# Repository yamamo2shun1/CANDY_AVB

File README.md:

# CANDY_AVB
## Description
This board is adopted Intel MAX10 series FPGA and Analog Devices SigmaDSP audio codec and then aimed at easier to prototyping and studying with a FPGA based on an audio signal and an ethernet.

A FPGA board in the market is too simple(it has only GPIO ports and
we have to make extended board by ourselves) or too high functionality
(DDR memory, HDMI, Gigabit ethernet...).

**I wanted simple FPGA board for sound and music.** So I started to develop this board.

## Specifications
* FPGA: Intel 10M16SAU(MAX10) x1
* SDRAM: Alliance Memory 64Mb(AS4C4M16SA-7BCN)
* ETH: TI DP83848 x1
* CODEC: Analog Devices ADAU1761 x2
* USB Serial: Silabs CP2102N x1
* CLOCK: 48MHz Crystal

## PCB

## Board

## Block Diagram

## License
<br /><span xmlns:dct="http://purl.org/dc/terms/" property="dct:title">CANDY_AVB</span> by <span xmlns:cc="http://creativecommons.org/ns#" property="cc:attributionName">Shunichi Yamamoto</span> is licensed under a <a rel="license" href="http://creativecommons.org/licenses/by/4.0/">Creative Commons Attribution 4.0 International License</a>.

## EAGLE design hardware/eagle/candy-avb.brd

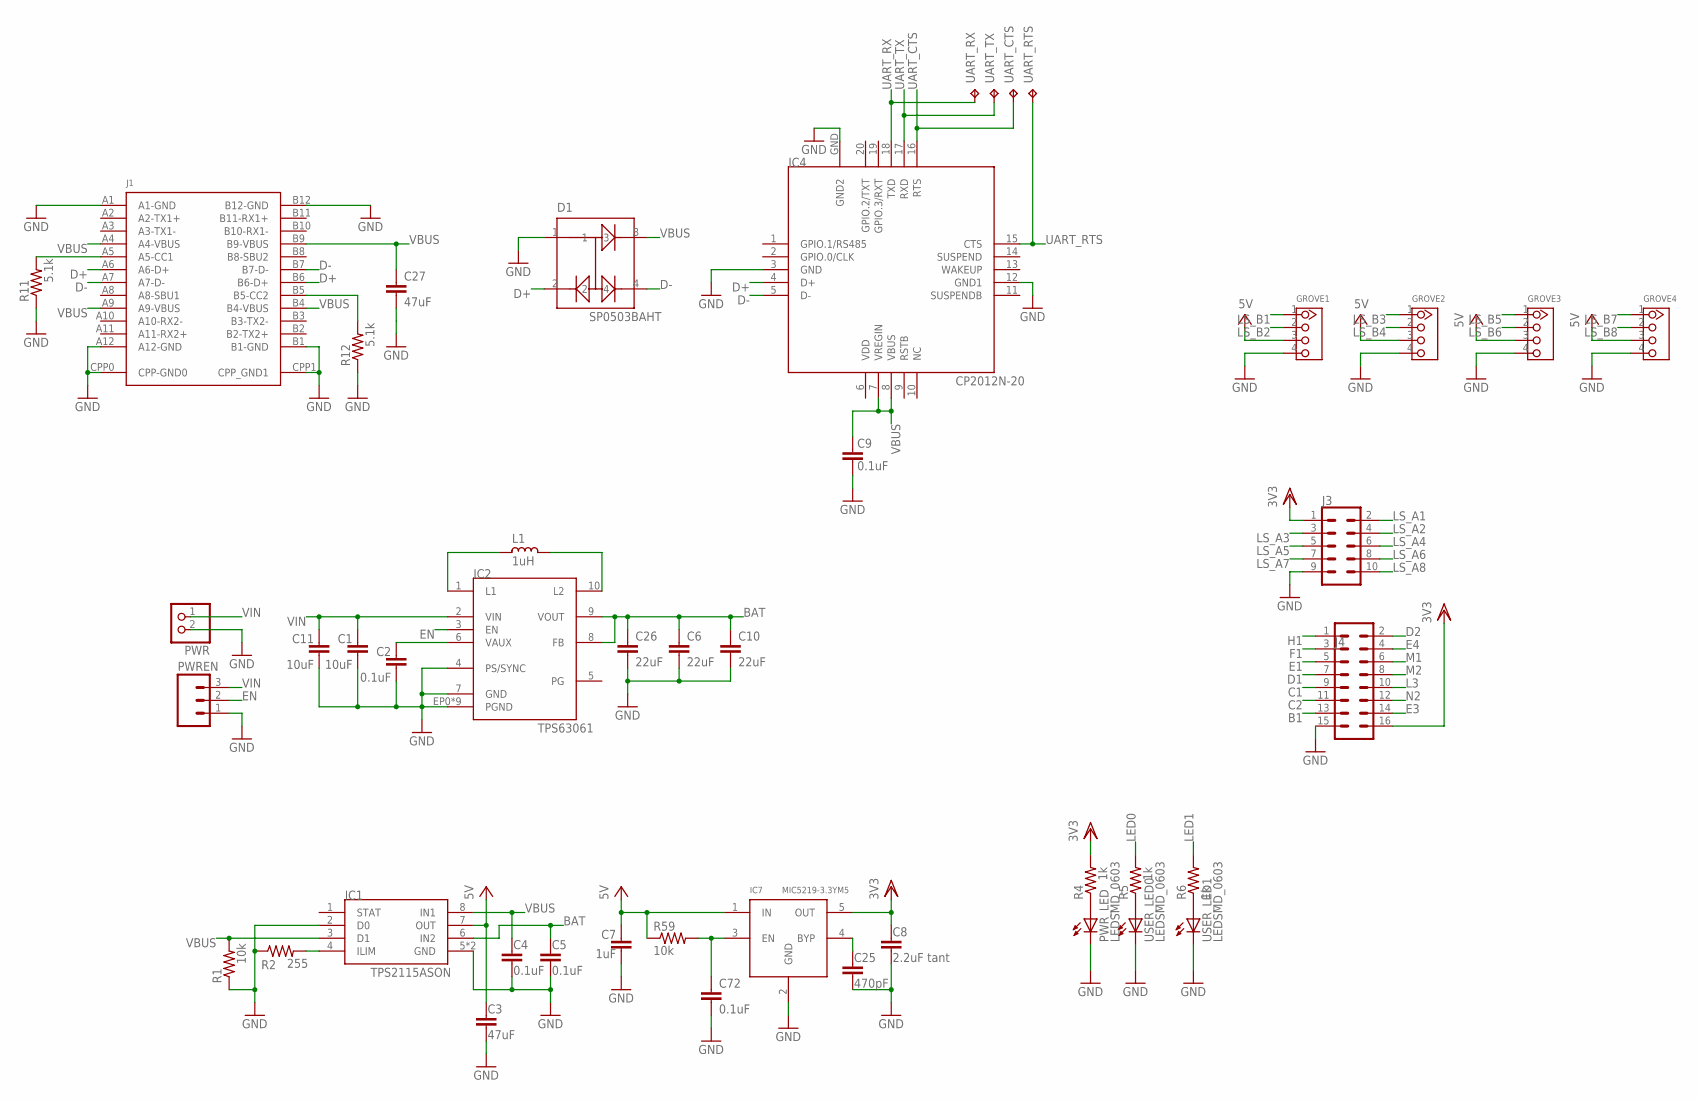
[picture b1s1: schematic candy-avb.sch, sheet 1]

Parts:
C1, C11: 10uF; C0805
C2, C4, C5, C9, C72: 0.1uF; C1608
C3, C27: 47uF; C1210
C6, C10, C26: 22uF; C0805
C7: 1uF; C1608
C8: 2.2uF tant; C1608
C25: 470pF; C1608
D1: SP0503BAHT; SOT143
GROVE1, GROVE2, GROVE3, GROVE4: 4P-2.0; SEEED_GROVE_4PIN_TH
IC1: TPS2115ASON; SON8
IC2: TPS63061; S-PDSO-N10
IC4: CP2012N-20; CP2102-QFN20
IC7: MIC5219-3.3YM5; SOT23-5
J1: USB_TYPEC_WE_632723
J3: CONN_05X2PTH; 2X5
J4: 2X6 FEMALE; 2X8
L1: 1uH; L4240
PWR: JST_2PIN-THM; JST-PH-2-THM
PWREN: M03PTH; 1X03
PWR_LED: LEDSMD_0603; CHIPLED_0603
R1, R59: 10k; 0402-RES
R2: 255; 0402-RES
R4, R5, R6: 1k; 0402-RES
R11, R12: 5.1k; 0402-RES
UART_CTS: TPB1,27; B1,27
UART_RTS: TPB1,27; B1,27
UART_RX: TPB1,27; B1,27
UART_TX: TPB1,27; B1,27
USER_LED0, USER_LED1: LEDSMD_0603; CHIPLED_0603

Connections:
B1: J4.13; also elsewhere on the board
BAT: C5.1, C6.1, C10.1, C26.1, IC1.6 (IN2), IC2.8 (FB), IC2.9 (VOUT)
C1: J4.9; also elsewhere on the board
C2: J4.11; also elsewhere on the board
D1: J4.7; also elsewhere on the board
D2: J4.2; also elsewhere on the board
D+: D1.2, IC4.4 (D+), J1.A6 (A6-D+), J1.B6 (B6-D+)
D-: D1.4, IC4.5 (D-), J1.A7 (A7-D-), J1.B7 (B7-D-)
E1: J4.5; also elsewhere on the board
E3: J4.14; also elsewhere on the board
E4: J4.4; also elsewhere on the board
EN: IC2.3 (EN), PWREN.2
EN1: C72.1, IC7.3 (EN), R59.2
F1: J4.3; also elsewhere on the board
GND: C1.2, C2.2, C3.2, C4.2, C5.2, C6.2, C7.2, C8.2, C9.2, C10.2, C11.2, C25.2, C26.2, C27.2, C72.2, D1.1, GROVE1.4, GROVE2.4, GROVE3.4, GROVE4.4, IC1.2 (D0), IC1.5 (GND), IC1.EP (GND), IC2.4 (PS/SYNC), IC2.7 (GND), IC2.EP0 (PGND), IC2.EP1 (PGND), IC2.EP2 (PGND), IC2.EP3 (PGND), IC2.EP4 (PGND), IC2.EP5 (PGND), IC2.EP6 (PGND), IC2.EP7 (PGND), IC2.EP8 (PGND), IC4.3 (GND), IC4.12 (GND1), IC4.GND (GND2), IC7.2 (GND), J1.A1 (A1-GND), J1.A12 (A12-GND), J1.B1 (B1-GND), J1.B12 (B12-GND), J1.CPP0 (CPP-GND0), J1.CPP1 (CPP_GND1), J3.9, J4.15, PWR.2 (1), PWREN.1, PWR_LED.C, R1.1, R2.1, R11.1, R12.1, USER_LED0.C, USER_LED1.C; also elsewhere on the board
H1: J4.1; also elsewhere on the board
L3: J4.10; also elsewhere on the board
LED0: R5.2; also elsewhere on the board
LED1: R6.2; also elsewhere on the board
LS_A1: J3.2; also elsewhere on the board
LS_A2: J3.4; also elsewhere on the board
LS_A3: J3.3; also elsewhere on the board
LS_A4: J3.6; also elsewhere on the board
LS_A5: J3.5; also elsewhere on the board
LS_A6: J3.8; also elsewhere on the board
LS_A7: J3.7; also elsewhere on the board
LS_A8: J3.10; also elsewhere on the board
LS_B1: GROVE1.1; also elsewhere on the board
LS_B2: GROVE1.2; also elsewhere on the board
LS_B3: GROVE2.1; also elsewhere on the board
LS_B4: GROVE2.2; also elsewhere on the board
LS_B5: GROVE3.1; also elsewhere on the board
LS_B6: GROVE3.2; also elsewhere on the board
LS_B7: GROVE4.1; also elsewhere on the board
LS_B8: GROVE4.2; also elsewhere on the board
M1: J4.6; also elsewhere on the board
M2: J4.8; also elsewhere on the board
N2: J4.12; also elsewhere on the board
unnamed: C2.1, IC2.6 (VAUX)
unnamed: C25.1, IC7.4 (BYP)
unnamed: PWR_LED.A, R4.1
unnamed: J1.A5 (A5-CC1), R11.2
unnamed: IC2.1 (L1), L1.2
unnamed: IC2.10 (L2), L1.1
unnamed: J1.B5 (B5-CC2), R12.2
unnamed: R6.1, USER_LED1.A
unnamed: R5.1, USER_LED0.A
unnamed: IC1.4 (ILIM), R2.2
UART_CTS: IC4.16 (RTS), UART_CTS.TP; also elsewhere on the board
UART_RTS: IC4.15 (CTS), UART_RTS.TP; also elsewhere on the board
UART_RX: IC4.18 (TXD), UART_RX.TP; also elsewhere on the board
UART_TX: IC4.17 (RXD), UART_TX.TP; also elsewhere on the board
VBUS: C4.1, C9.1, C27.1, D1.3, IC1.3 (D1), IC1.8 (IN1), IC4.7 (VREGIN), IC4.8 (VBUS), J1.A4 (A4-VBUS), J1.A9 (A9-VBUS), J1.B4 (B4-VBUS), J1.B9 (B9-VBUS), R1.2
VCC: C3.1, C7.1, GROVE1.3, GROVE2.3, GROVE3.3, GROVE4.3, IC1.7 (OUT), IC7.1 (IN), R59.1; also elsewhere on the board
VDD: C8.1, IC4.6 (VDD), IC7.5 (OUT), J3.1, J4.16, R4.2; also elsewhere on the board
VIN: C1.1, C11.1, IC2.2 (VIN), PWR.1 (2), PWREN.3

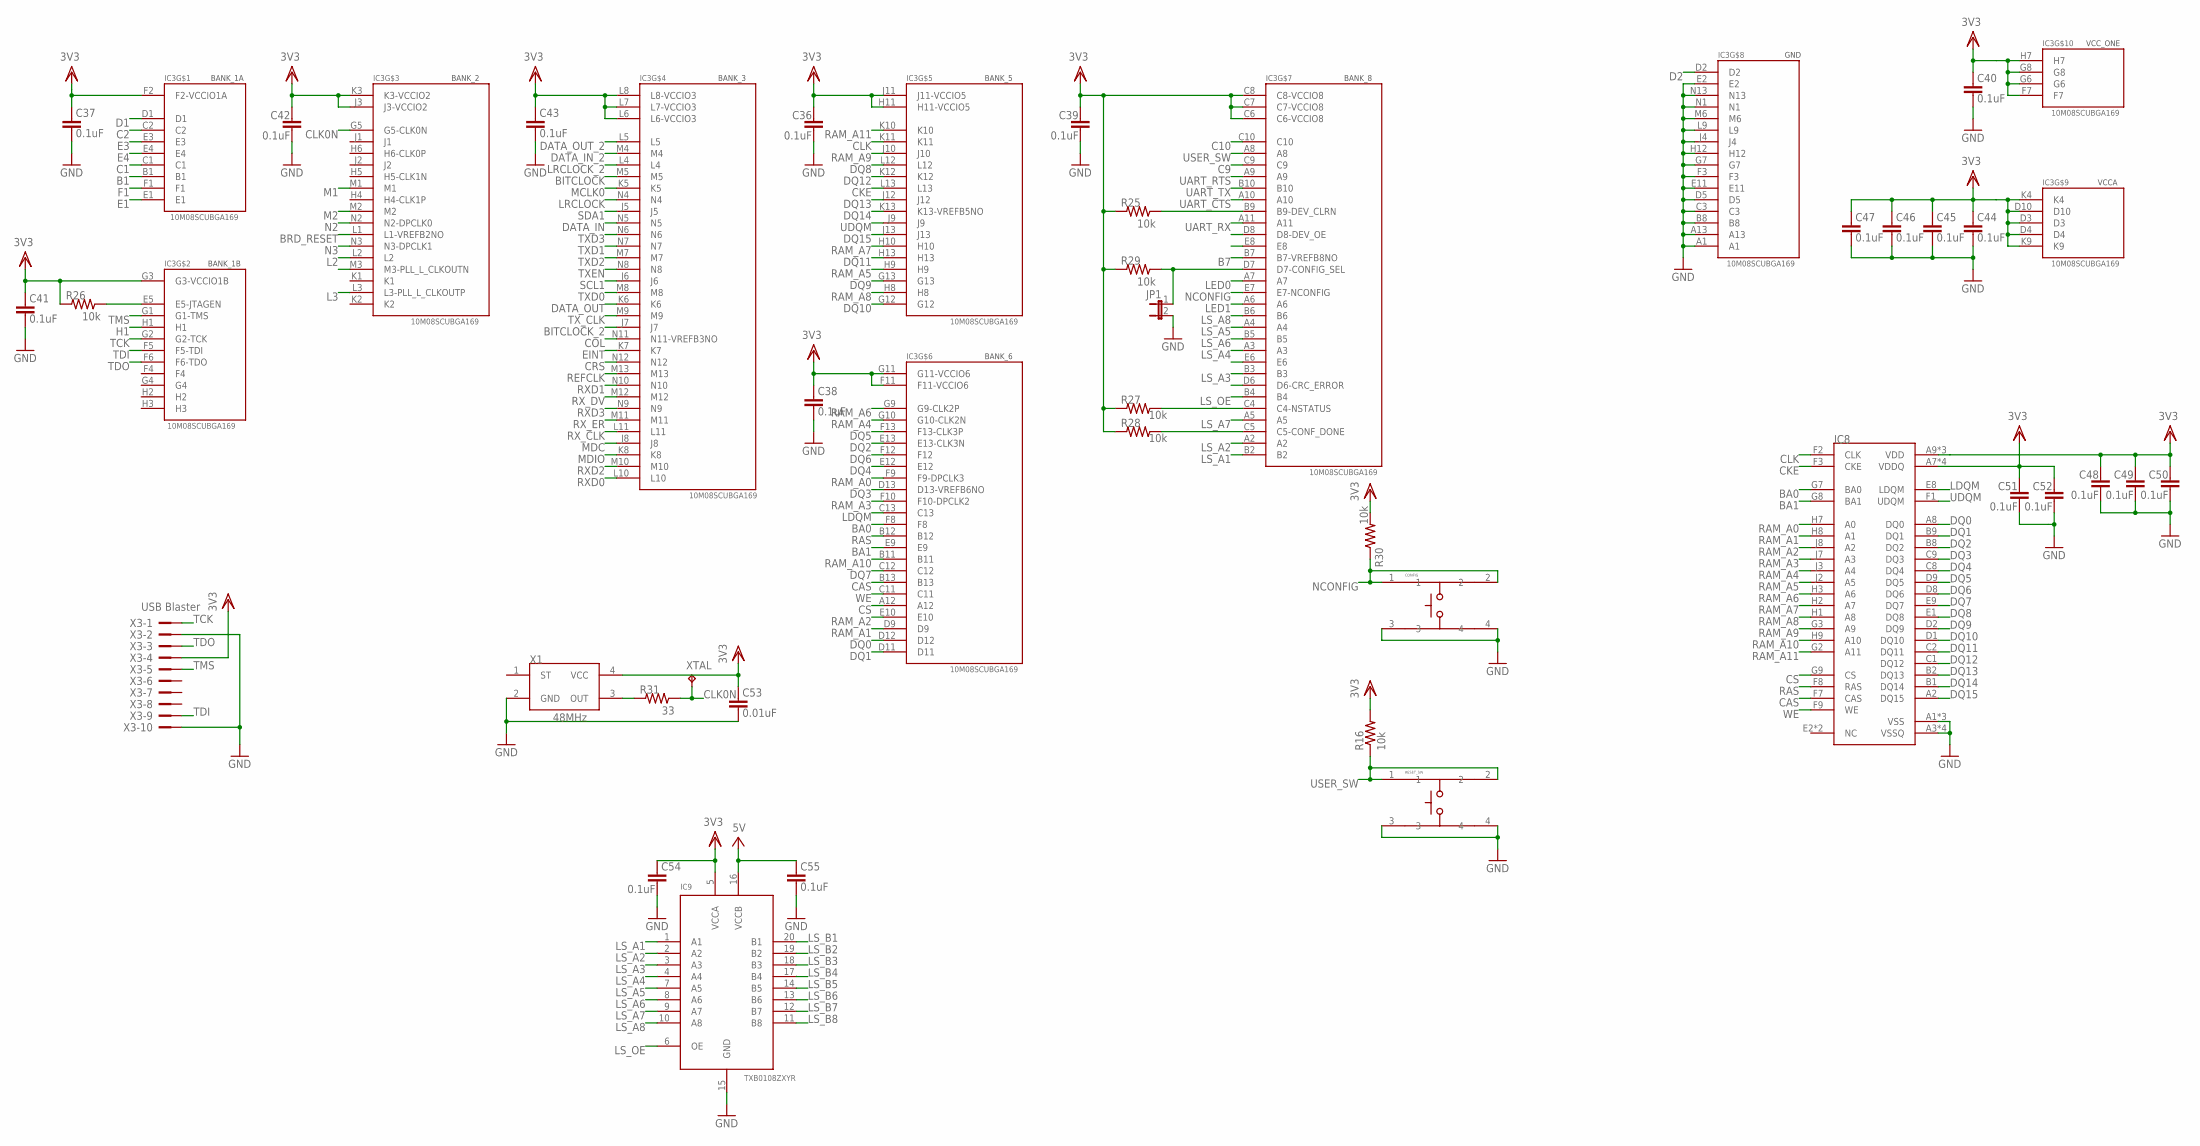
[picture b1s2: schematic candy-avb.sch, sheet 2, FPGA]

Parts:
C36, C37, C38, C39, C40, C41, C42, C43, C44, C45, C46, C47, C48, C49, C50, C51, C52, C54, C55: 0.1uF; C0402
C53: 0.01uF; C0402
CONFIG: TACTILE_SW_4PINSKRPABE010; SKRPABE010
IC3: 10M08SCUBGA169; MBGA169-MAX10
IC8: AS4C4M16SAFBGA54; FBGA54-AS4C4M16SA
IC9: TXB0108ZXYR; USON20
JP1: JUMPER-2SMD-NO; SJ_2S-NO
R16, R25, R26, R27, R28, R29, R30: 10k; 0402-RES
R31: 33; 0402-RES
RESET_SW: TACTILE_SW_4PINSKRPABE010; SKRPABE010
X1: 48MHz; SMD3225_4_EPSON
X3: USB Blaster; PAK100/2500-10
XTAL: TPPAD1-13; P1-13

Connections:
B1: IC3.B1; also elsewhere on the board
B7: IC3.B7 (B7-VREFB8NO)
BA0: IC3.F8, IC8.G7 (BA0)
BA1: IC3.E9, IC8.G8 (BA1)
BITCLOCK: IC3.M5; also elsewhere on the board
BITCLOCK_2: IC3.J7; also elsewhere on the board
BRD_RESET: IC3.L1 (L1-VREFB2NO); also elsewhere on the board
C1: IC3.C1; also elsewhere on the board
C2: IC3.C2; also elsewhere on the board
C9: IC3.C9
C10: IC3.C10
CAS: IC3.B13, IC8.F7 (CAS)
CKE: IC3.L13, IC8.F3 (CKE)
CLK: IC3.K11, IC8.F2 (CLK)
CLK0N: IC3.G5 (G5-CLK0N), R31.1, XTAL.TP
COL: IC3.N11 (N11-VREFB3NO); also elsewhere on the board
CRS: IC3.N12; also elsewhere on the board
CS: IC3.A12, IC8.G9 (CS)
D1: IC3.D1; also elsewhere on the board
D2: IC3.D2; also elsewhere on the board
DATA_IN: IC3.N5; also elsewhere on the board
DATA_IN_2: IC3.M4; also elsewhere on the board
DATA_OUT: IC3.K6; also elsewhere on the board
DATA_OUT_2: IC3.L5; also elsewhere on the board
DQ0: IC3.D12, IC8.A8 (DQ0)
DQ1: IC3.D11, IC8.B9 (DQ1)
DQ2: IC3.E13 (E13-CLK3N), IC8.B8 (DQ2)
DQ3: IC3.D13 (D13-VREFB6NO), IC8.C9 (DQ3)
DQ4: IC3.E12, IC8.C8 (DQ4)
DQ5: IC3.F13 (F13-CLK3P), IC8.D9 (DQ5)
DQ6: IC3.F12, IC8.D8 (DQ6)
DQ7: IC3.C12, IC8.E9 (DQ7)
DQ8: IC3.L12, IC8.E1 (DQ8)
DQ9: IC3.G13, IC8.D2 (DQ9)
DQ10: IC3.G12, IC8.D1 (DQ10)
DQ11: IC3.H13, IC8.C2 (DQ11)
DQ12: IC3.K12, IC8.C1 (DQ12)
DQ13: IC3.J12, IC8.B2 (DQ13)
DQ14: IC3.K13 (K13-VREFB5NO), IC8.B1 (DQ14)
DQ15: IC3.J13, IC8.A2 (DQ15)
E1: IC3.E1; also elsewhere on the board
E3: IC3.E3; also elsewhere on the board
E4: IC3.E4; also elsewhere on the board
EINT: IC3.K7; also elsewhere on the board
F1: IC3.F1; also elsewhere on the board
GND: C36.2, C37.2, C38.2, C39.2, C40.2, C41.2, C42.2, C43.2, C44.2, C45.2, C46.2, C47.2, C48.2, C49.2, C50.2, C51.2, C52.2, C53.2, C54.2, C55.2, CONFIG.3, CONFIG.4, IC3.A1, IC3.A13, IC3.B8, IC3.C3, IC3.D5, IC3.E2, IC3.E11, IC3.F3, IC3.G7, IC3.H12, IC3.J4, IC3.L9, IC3.M6, IC3.N1, IC3.N13, IC8.A1 (VSS), IC8.A3 (VSSQ), IC8.B7 (VSSQ), IC8.C3 (VSSQ), IC8.D7 (VSSQ), IC8.E3 (VSS), IC8.J1 (VSS), IC9.15 (GND), JP1.2, RESET_SW.3, RESET_SW.4, X1.2 (GND), X3.2, X3.10; also elsewhere on the board
H1: IC3.H1; also elsewhere on the board
L2: IC3.L2
L3: IC3.L3 (L3-PLL_L_CLKOUTP); also elsewhere on the board
LDQM: IC3.C13, IC8.E8 (LDQM)
LED0: IC3.A7; also elsewhere on the board
LED1: IC3.A6; also elsewhere on the board
LRCLOCK: IC3.N4; also elsewhere on the board
LRCLOCK_2: IC3.L4; also elsewhere on the board
LS_A1: IC3.B2, IC9.1 (A1); also elsewhere on the board
LS_A2: IC3.A2, IC9.2 (A2); also elsewhere on the board
LS_A3: IC3.B3, IC9.3 (A3); also elsewhere on the board
LS_A4: IC3.A3, IC9.4 (A4); also elsewhere on the board
LS_A5: IC3.A4, IC9.7 (A5); also elsewhere on the board
LS_A6: IC3.B5, IC9.8 (A6); also elsewhere on the board
LS_A7: IC3.A5, IC9.9 (A7); also elsewhere on the board
LS_A8: IC3.B6, IC9.10 (A8); also elsewhere on the board
LS_B1: IC9.20 (B1); also elsewhere on the board
LS_B2: IC9.19 (B2); also elsewhere on the board
LS_B3: IC9.18 (B3); also elsewhere on the board
LS_B4: IC9.17 (B4); also elsewhere on the board
LS_B5: IC9.14 (B5); also elsewhere on the board
LS_B6: IC9.13 (B6); also elsewhere on the board
LS_B7: IC9.12 (B7); also elsewhere on the board
LS_B8: IC9.11 (B8); also elsewhere on the board
LS_OE: IC3.B4, IC9.6 (OE)
M1: IC3.M1; also elsewhere on the board
M2: IC3.M2; also elsewhere on the board
MCLK0: IC3.K5; also elsewhere on the board
MDC: IC3.J8; also elsewhere on the board
MDIO: IC3.K8; also elsewhere on the board
N2: IC3.N2 (N2-DPCLK0); also elsewhere on the board
N3: IC3.N3 (N3-DPCLK1)
unnamed: IC3.E5 (E5-JTAGEN), R26.1
unnamed: IC3.B9 (B9-DEV_CLRN), R25.1
unnamed: IC3.C4 (C4-NSTATUS), R27.1
unnamed: IC3.C5 (C5-CONF_DONE), R28.1
unnamed: IC3.D7 (D7-CONFIG_SEL), JP1.1, R29.1
unnamed: R31.2, X1.3 (OUT)
NCONFIG: CONFIG.1, CONFIG.2, IC3.E7 (E7-NCONFIG), R30.1
RAM_A0: IC3.F9 (F9-DPCLK3), IC8.H7 (A0)
RAM_A1: IC3.D9, IC8.H8 (A1)
RAM_A2: IC3.E10, IC8.J8 (A2)
RAM_A3: IC3.F10 (F10-DPCLK2), IC8.J7 (A3)
RAM_A4: IC3.G10 (G10-CLK2N), IC8.J3 (A4)
RAM_A5: IC3.H9, IC8.J2 (A5)
RAM_A6: IC3.G9 (G9-CLK2P), IC8.H3 (A6)
RAM_A7: IC3.H10, IC8.H2 (A7)
RAM_A8: IC3.H8, IC8.H1 (A8)
RAM_A9: IC3.J10, IC8.G3 (A9)
RAM_A10: IC3.B11, IC8.H9 (A10)
RAM_A11: IC3.K10, IC8.G2 (A11)
RAS: IC3.B12, IC8.F8 (RAS)
REFCLK: IC3.M13; also elsewhere on the board
RXD0: IC3.L10; also elsewhere on the board
RXD1: IC3.N10; also elsewhere on the board
RXD2: IC3.M10; also elsewhere on the board
RXD3: IC3.N9; also elsewhere on the board
RX_CLK: IC3.L11; also elsewhere on the board
RX_DV: IC3.M12; also elsewhere on the board
RX_ER: IC3.M11; also elsewhere on the board
SCL1: IC3.J6; also elsewhere on the board
SDA1: IC3.J5; also elsewhere on the board
TCK: IC3.G2 (G2-TCK), X3.1
TDI: IC3.F5 (F5-TDI), X3.9
TDO: IC3.F6 (F6-TDO), X3.3
TMS: IC3.G1 (G1-TMS), X3.5
TXD0: IC3.M8; also elsewhere on the board
TXD1: IC3.N7; also elsewhere on the board
TXD2: IC3.M7; also elsewhere on the board
TXD3: IC3.N6; also elsewhere on the board
TXEN: IC3.N8; also elsewhere on the board
TX_CLK: IC3.M9; also elsewhere on the board
UART_CTS: IC3.A10; also elsewhere on the board
UART_RTS: IC3.A9; also elsewhere on the board
UART_RX: IC3.A11; also elsewhere on the board
UART_TX: IC3.B10; also elsewhere on the board
UDQM: IC3.J9, IC8.F1 (UDQM)
USER_SW: IC3.A8, R16.1, RESET_SW.1, RESET_SW.2
VCC: C55.1, IC9.16 (VCCB); also elsewhere on the board
VDD: C36.1, C37.1, C38.1, C39.1, C40.1, C41.1, C42.1, C43.1, C44.1, C45.1, C46.1, C47.1, C48.1, C49.1, C50.1, C51.1, C52.1, C53.1, C54.1, IC3.C6 (C6-VCCIO8), IC3.C7 (C7-VCCIO8), IC3.C8 (C8-VCCIO8), IC3.D3, IC3.D4, IC3.D10, IC3.F2 (F2-VCCIO1A), IC3.F7, IC3.F11 (F11-VCCIO6), IC3.G3 (G3-VCCIO1B), IC3.G6, IC3.G8, IC3.G11 (G11-VCCIO6), IC3.H7, IC3.H11 (H11-VCCIO5), IC3.J3 (J3-VCCIO2), IC3.J11 (J11-VCCIO5), IC3.K3 (K3-VCCIO2), IC3.K4, IC3.K9, IC3.L6 (L6-VCCIO3), IC3.L7 (L7-VCCIO3), IC3.L8 (L8-VCCIO3), IC8.A7 (VDDQ), IC8.A9 (VDD), IC8.B3 (VDDQ), IC8.C7 (VDDQ), IC8.D3 (VDDQ), IC8.E7 (VDD), IC8.J9 (VDD), IC9.5 (VCCA), R16.2, R25.2, R26.2, R27.2, R28.2, R29.2, R30.2, X1.4 (VCC), X3.4; also elsewhere on the board
WE: IC3.C11, IC8.F9 (WE)

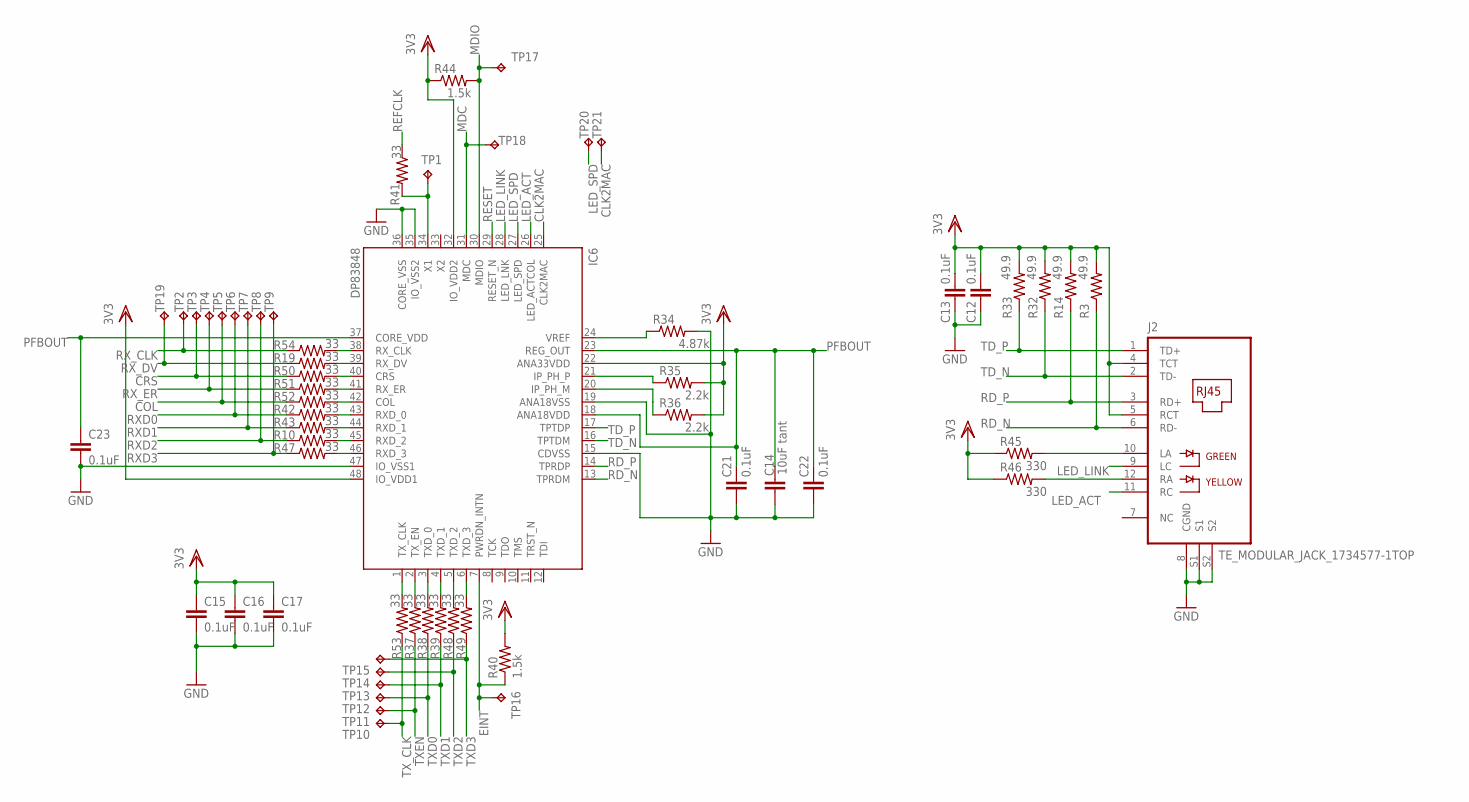
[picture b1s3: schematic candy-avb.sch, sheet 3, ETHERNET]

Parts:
C12, C13, C15, C16, C17, C21, C22, C23: 0.1uF; C0402
C14: 10uF tant; C0603
IC6: DP83848; LQFP48
J2: TE_MODULAR_JACK_1734577-1TOP; TE_MODULAR_JACK_1734577-1
R3, R14, R32, R33: 49.9; 0402-RES
R10, R19, R37, R38, R39, R41, R42, R43, R47, R48, R49, R50, R51, R52, R53, R54: 33; 0402-RES
R34: 4.87k; 0402-RES
R35, R36: 2.2k; 0402-RES
R40, R44: 1.5k; 0402-RES
R45, R46: 330; 0402-RES
TP1: TPPAD1-13; P1-13
TP2, TP3, TP4, TP5, TP6, TP7, TP8, TP9, TP10, TP11, TP12, TP13, TP14, TP15, TP16, TP17, TP18, TP19, TP20, TP21: TPB1,27; B1,27

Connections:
CLK2MAC: IC6.25 (CLK2MAC), TP21.TP
COL: R52.1, TP5.TP; also elsewhere on the board
CRS: R50.1, TP3.TP; also elsewhere on the board
EINT: IC6.7 (PWRDN_INTN), R40.1, TP16.TP; also elsewhere on the board
GND: C12.2, C13.2, C14.2, C15.2, C16.2, C17.2, C21.2, C22.2, C23.2, IC6.15 (CDVSS), IC6.19 (ANA18VSS), IC6.35 (IO_VSS2), IC6.36 (CORE_VSS), IC6.47 (IO_VSS1), J2.8 (CGND), J2.S1, J2.S2, R34.2; also elsewhere on the board
LED_ACT: IC6.26 (LED_ACTCOL), J2.11 (RC)
LED_LINK: IC6.28 (LED_LNK), J2.9 (LC)
LED_SPD: IC6.27 (LED_SPD), TP20.TP
MDC: IC6.31 (MDC), TP18.TP; also elsewhere on the board
MDIO: IC6.30 (MDIO), R44.2, TP17.TP; also elsewhere on the board
unnamed: IC6.20 (IP_PH_M), R36.1
unnamed: IC6.39 (RX_DV), R19.2
unnamed: IC6.4 (TXD_1), R39.2
unnamed: IC6.45 (RXD_2), R10.2
unnamed: IC6.46 (RXD_3), R47.2
unnamed: IC6.3 (TXD_0), R38.2
unnamed: IC6.2 (TX_EN), R37.2
unnamed: IC6.34 (X1), R41.2, TP1.TP
unnamed: IC6.43 (RXD_0), R42.2
unnamed: IC6.5 (TXD_2), R48.2
unnamed: J2.10 (LA), R45.2
unnamed: J2.12 (RA), R46.2
unnamed: IC6.44 (RXD_1), R43.2
unnamed: IC6.21 (IP_PH_P), R35.1
unnamed: IC6.24 (VREF), R34.1
unnamed: IC6.6 (TXD_3), R49.2
unnamed: IC6.42 (COL), R52.2
unnamed: IC6.41 (RX_ER), R51.2
unnamed: IC6.40 (CRS), R50.2
unnamed: IC6.38 (RX_CLK), R54.2
PFBOUT: C14.1, C21.1, C22.1, C23.1, IC6.18 (ANA18VDD), IC6.23 (REG_OUT), IC6.37 (CORE_VDD)
RD_N: IC6.13 (TPRDM), J2.6 (RD-), R3.1
RD_P: IC6.14 (TPRDP), J2.3 (RD+), R14.1
REFCLK: R41.1; also elsewhere on the board
RESET: IC6.29 (RESET_N)
RXD0: R42.1, TP6.TP; also elsewhere on the board
RXD1: R43.1, TP7.TP; also elsewhere on the board
RXD2: R10.1, TP8.TP; also elsewhere on the board
RXD3: R47.1, TP9.TP; also elsewhere on the board
RX_CLK: R54.1, TP2.TP; also elsewhere on the board
RX_DV: R19.1, TP19.TP; also elsewhere on the board
RX_ER: R51.1, TP4.TP; also elsewhere on the board
TD_N: IC6.16 (TPTDM), J2.2 (TD-), R32.1
TD_P: IC6.17 (TPTDP), J2.1 (TD+), R33.1
TXCLK: IC6.1 (TX_CLK), R53.2
TXD0: R38.1, TP12.TP; also elsewhere on the board
TXD1: R39.1, TP13.TP; also elsewhere on the board
TXD2: R48.1, TP14.TP; also elsewhere on the board
TXD3: R49.1, TP15.TP; also elsewhere on the board
TXEN: R37.1, TP11.TP; also elsewhere on the board
TX_CLK: R53.1, TP10.TP; also elsewhere on the board
VDD: C12.1, C13.1, C15.1, C16.1, C17.1, IC6.22 (ANA33VDD), IC6.32 (IO_VDD2), IC6.48 (IO_VDD1), J2.4 (TCT), J2.5 (RCT), R3.2, R14.2, R32.2, R33.2, R35.2, R36.2, R40.2, R44.1, R45.1, R46.1; also elsewhere on the board

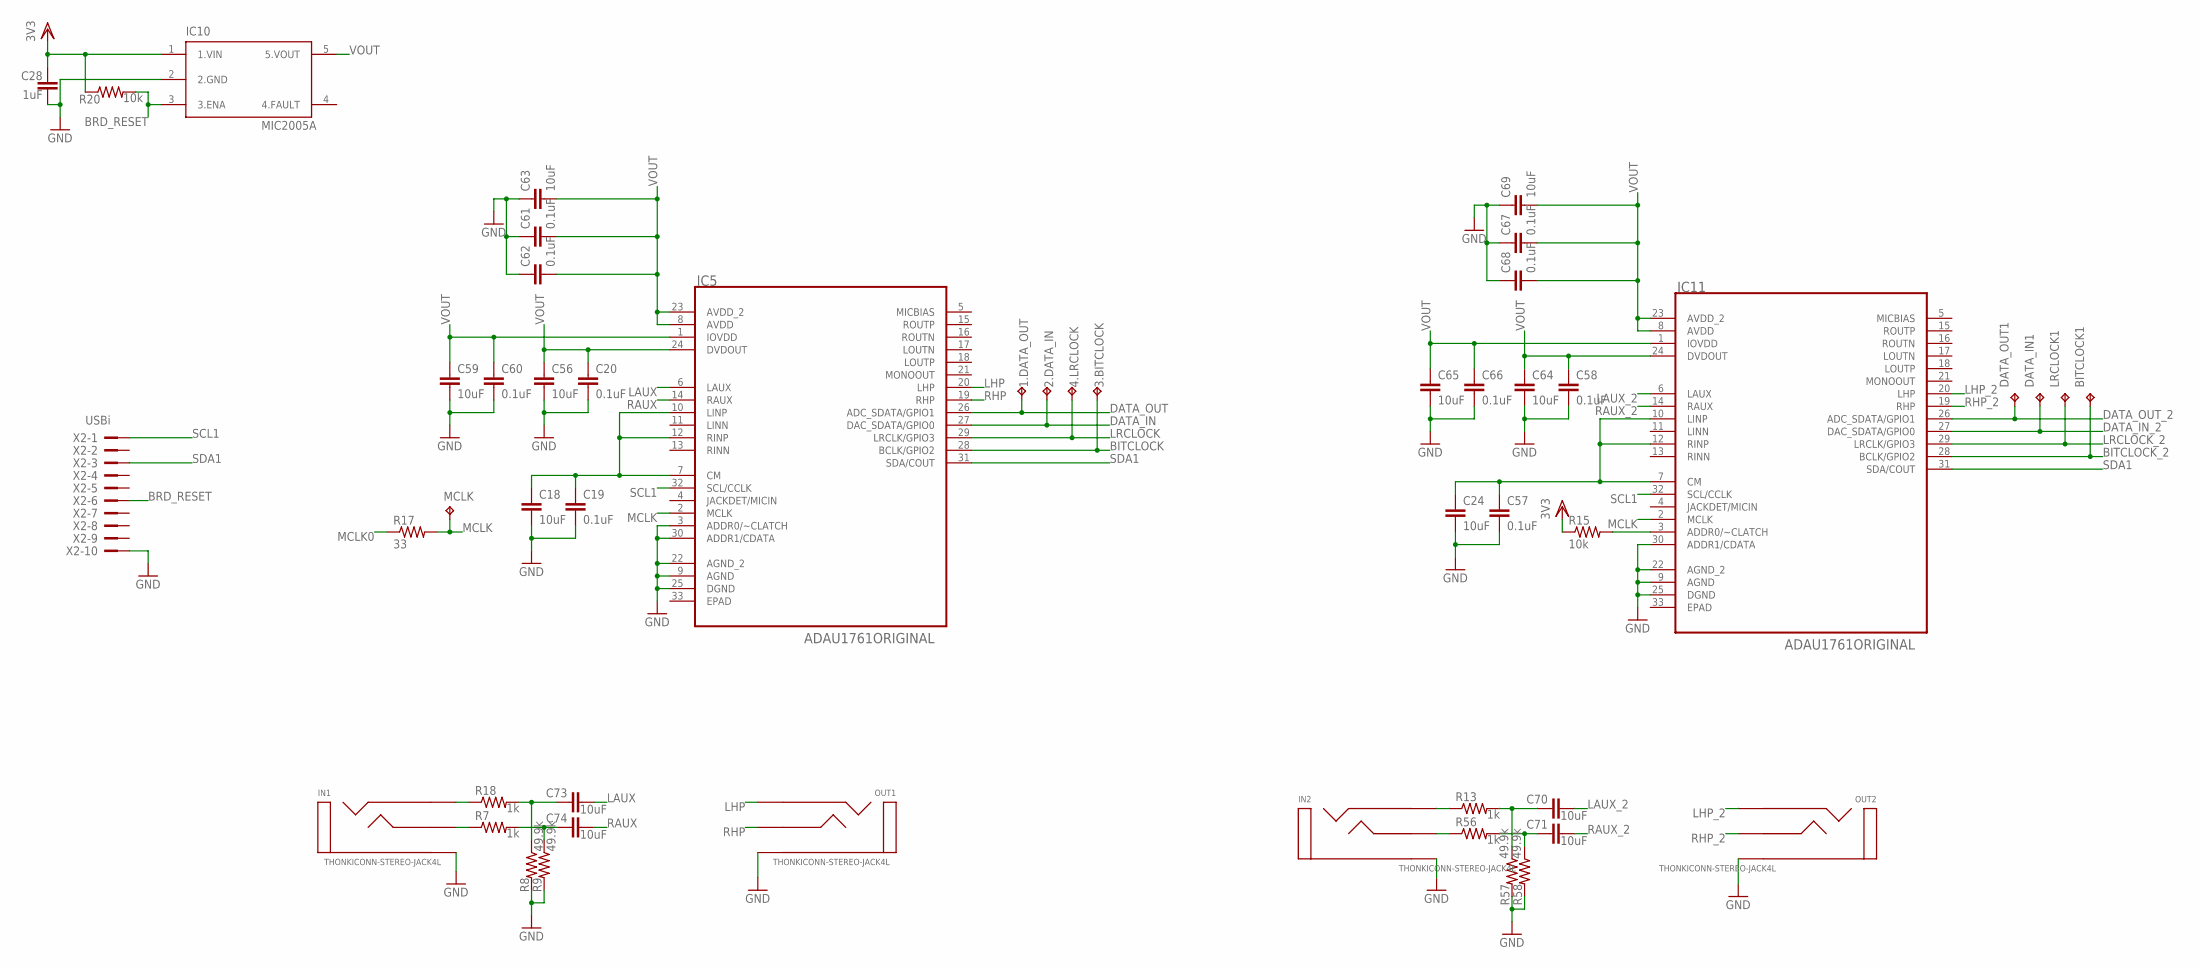
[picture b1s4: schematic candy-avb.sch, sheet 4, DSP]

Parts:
1.DATA_OUT, 2.DATA_IN, 3.BITCLOCK, 4.LRCLOCK: TPB1,27; B1,27
BITCLOCK1: TPB1,27; B1,27
C18, C24, C56, C59, C63, C64, C65, C69: 10uF; C0603
C19, C20, C57, C58, C60, C61, C62, C66, C67, C68: 0.1uF; C0402
C28: 1uF; C0603
C70, C71, C73, C74: 10uF; C1608
DATA_IN1: TPB1,27; B1,27
DATA_OUT1: TPB1,27; B1,27
IC5, IC11: ADAU1761ORIGINAL; QFN50_500X500_33_O
IC10: MIC2005A; SOT23-5
IN1, IN2: THONKICONN-STEREO-JACK4L; THONKICONN-JACK-4
LRCLOCK1: TPB1,27; B1,27
MCLK: TPPAD1-13; P1-13
OUT1, OUT2: THONKICONN-STEREO-JACK4L; THONKICONN-JACK-4
R7, R13, R18, R56: 1k; 0402-RES
R8, R9, R57, R58: 49.9k; 0402-RES
R15, R20: 10k; 0402-RES
R17: 33; 0402-RES
X2: USBi; PAK100/2500-10

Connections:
BITCLOCK: 3.BITCLOCK.TP, IC5.28 (BCLK/GPIO2); also elsewhere on the board
BITCLOCK_2: BITCLOCK1.TP, IC11.28 (BCLK/GPIO2); also elsewhere on the board
BRD_RESET: IC10.3 (3.ENA), R20.2, X2.6; also elsewhere on the board
DATA_IN: 2.DATA_IN.TP, IC5.27 (DAC_SDATA/GPIO0); also elsewhere on the board
DATA_IN_2: DATA_IN1.TP, IC11.27 (DAC_SDATA/GPIO0); also elsewhere on the board
DATA_OUT: 1.DATA_OUT.TP, IC5.26 (ADC_SDATA/GPIO1); also elsewhere on the board
DATA_OUT_2: DATA_OUT1.TP, IC11.26 (ADC_SDATA/GPIO1); also elsewhere on the board
GND: C18.2, C19.2, C20.2, C24.2, C28.2, C56.2, C57.2, C58.2, C59.2, C60.2, C61.1, C62.1, C63.1, C64.2, C65.2, C66.2, C67.1, C68.1, C69.1, IC5.3 (ADDR0/~CLATCH), IC5.9 (AGND), IC5.22 (AGND_2), IC5.25 (DGND), IC5.30 (ADDR1/CDATA), IC10.2 (2.GND), IC11.9 (AGND), IC11.22 (AGND_2), IC11.25 (DGND), IC11.30 (ADDR1/CDATA), IN1.1B (1.SLEEVE), IN1.1T (1.SLEEVE), IN2.1B (1.SLEEVE), IN2.1T (1.SLEEVE), OUT1.1B (1.SLEEVE), OUT1.1T (1.SLEEVE), OUT2.1B (1.SLEEVE), OUT2.1T (1.SLEEVE), R8.2, R9.2, R57.2, R58.2, X2.10; also elsewhere on the board
LAUX: C73.2, IC5.6 (LAUX)
LAUX_2: C70.2, IC11.6 (LAUX)
LHP: IC5.20 (LHP), OUT1.3B (3.RING), OUT1.3T (3.RING)
LHP_2: IC11.20 (LHP), OUT2.3B (3.RING), OUT2.3T (3.RING)
LRCLOCK: 4.LRCLOCK.TP, IC5.29 (LRCLK/GPIO3); also elsewhere on the board
LRCLOCK_2: IC11.29 (LRCLK/GPIO3), LRCLOCK1.TP; also elsewhere on the board
MCLK: IC5.2 (MCLK), IC11.2 (MCLK), MCLK.TP, R17.2
MCLK0: R17.1; also elsewhere on the board
unnamed: IC11.3 (ADDR0/~CLATCH), R15.2
unnamed: C18.1, C19.1, IC5.7 (CM), IC5.10 (LINP), IC5.12 (RINP)
unnamed: IN1.3B (3.RING), IN1.3T (3.RING), R18.1
unnamed: IN1.2B (2.TIP), IN1.2T (2.TIP), R7.1
unnamed: C24.1, C57.1, IC11.7 (CM), IC11.10 (LINP), IC11.12 (RINP)
unnamed: C70.1, R13.2, R57.1
unnamed: C71.1, R56.2, R58.1
unnamed: IN2.3B (3.RING), IN2.3T (3.RING), R13.1
unnamed: IN2.2B (2.TIP), IN2.2T (2.TIP), R56.1
unnamed: C73.1, R8.1, R18.2
unnamed: C74.1, R7.2, R9.1
RAUX: C74.2, IC5.14 (RAUX)
RAUX_2: C71.2, IC11.14 (RAUX)
RHP: IC5.19 (RHP), OUT1.2B (2.TIP), OUT1.2T (2.TIP)
RHP_2: IC11.19 (RHP), OUT2.2B (2.TIP), OUT2.2T (2.TIP)
SCL1: IC5.32 (SCL/CCLK), IC11.32 (SCL/CCLK), X2.1; also elsewhere on the board
SDA1: IC5.31 (SDA/COUT), IC11.31 (SDA/COUT), X2.3; also elsewhere on the board
VDD: C28.1, IC10.1 (1.VIN), R15.1, R20.1; also elsewhere on the board
VOUT: C20.1, C56.1, C58.1, C59.1, C60.1, C61.2, C62.2, C63.2, C64.1, C65.1, C66.1, C67.2, C68.2, C69.2, IC5.1 (IOVDD), IC5.8 (AVDD), IC5.23 (AVDD_2), IC5.24 (DVDOUT), IC10.5 (5.VOUT), IC11.1 (IOVDD), IC11.8 (AVDD), IC11.23 (AVDD_2), IC11.24 (DVDOUT)

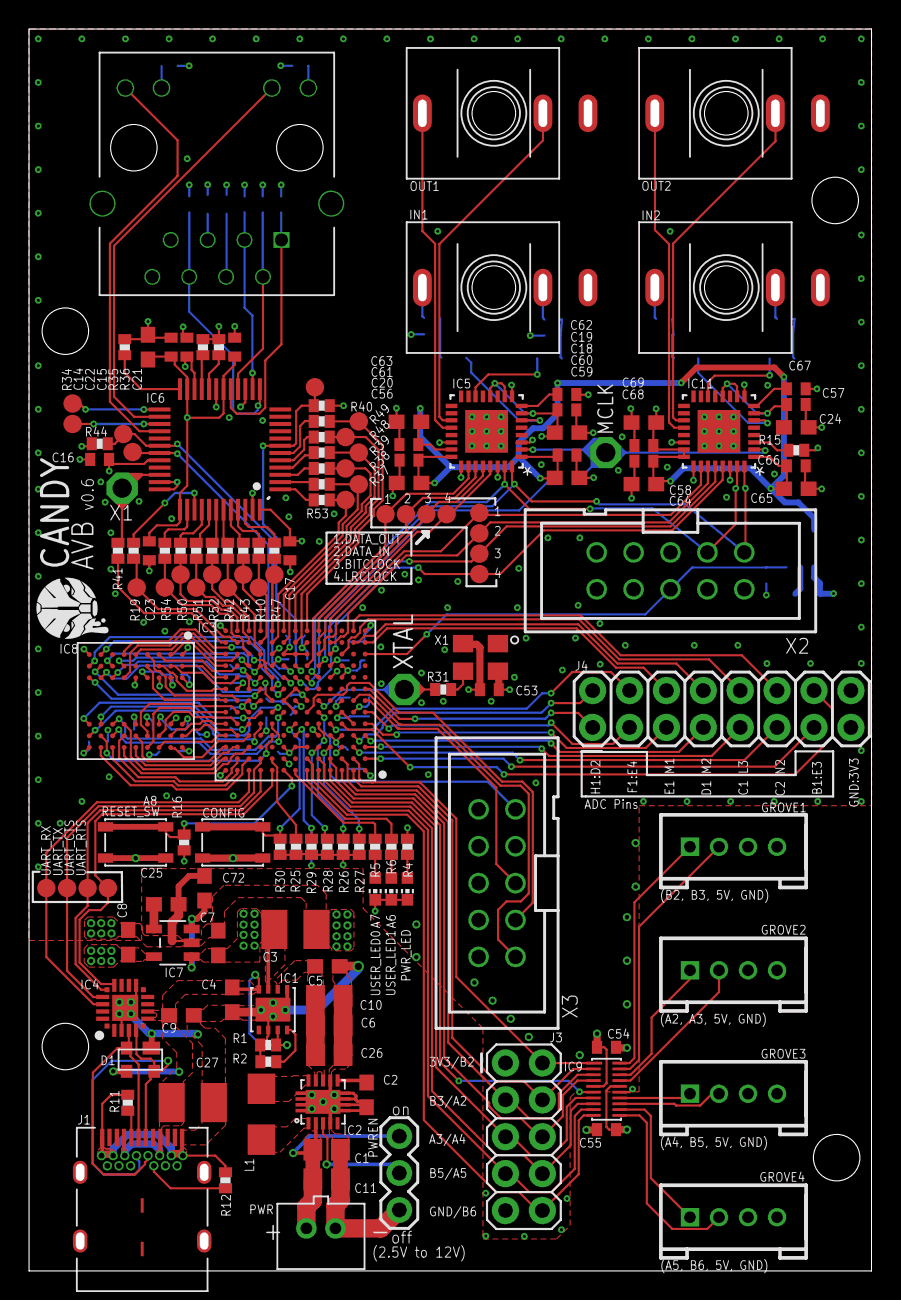
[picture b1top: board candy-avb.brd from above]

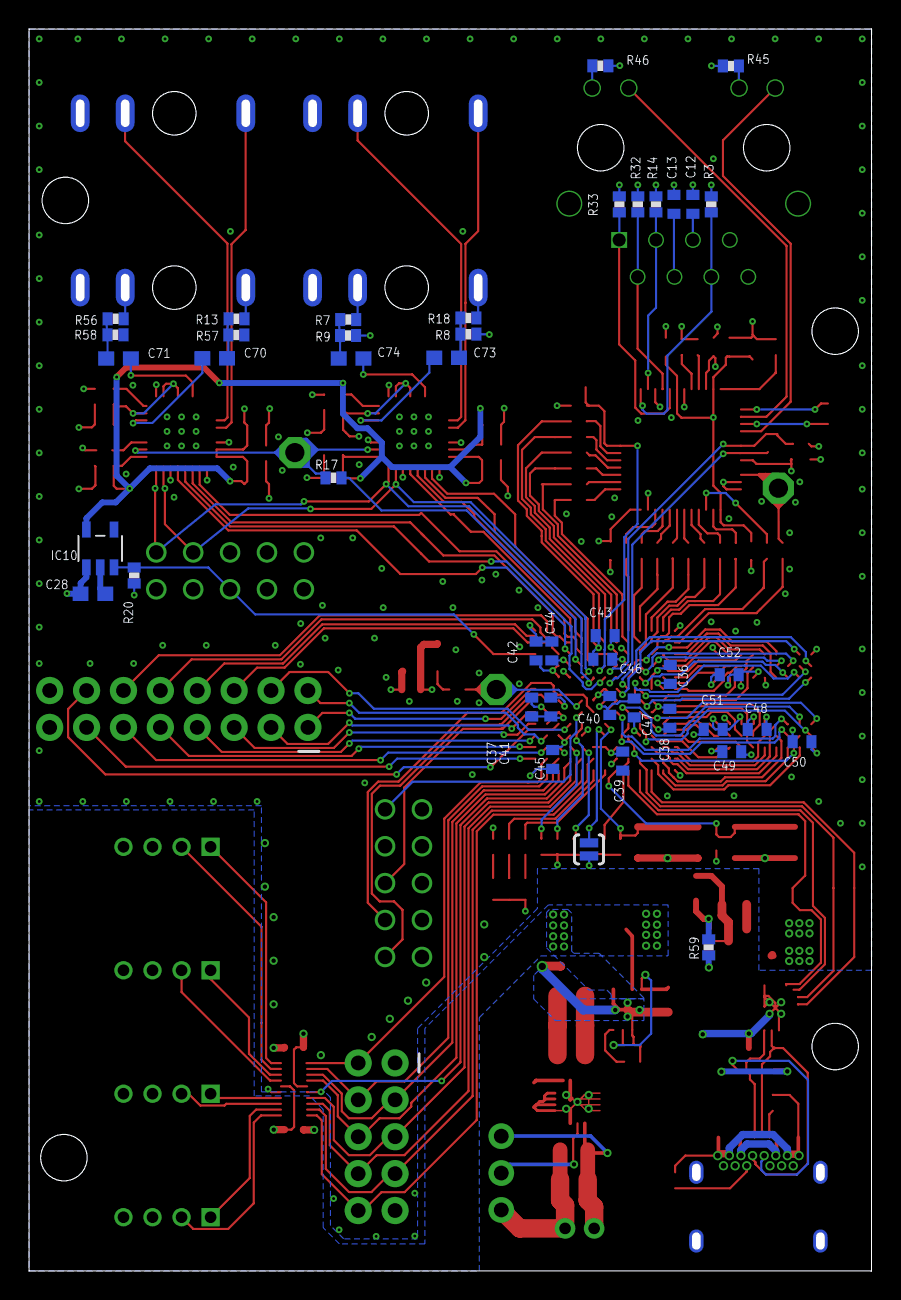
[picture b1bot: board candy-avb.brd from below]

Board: 4 copper layers, 58.0 x 85.5 mm, 193 parts (43 on the bottom side), 190 nets.

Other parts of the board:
U$2: CANDY-ICON

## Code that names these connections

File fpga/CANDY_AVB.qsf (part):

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set_global_assignment -name INTERNAL_FLASH_UPDATE_MODE "SINGLE IMAGE"
set_location_assignment PIN_K5 -to CODEC_CLKOUT
set_location_assignment PIN_M13 -to ETH_CLKOUT
set_location_assignment PIN_B10 -to UART_TX
set_location_assignment PIN_A11 -to UART_RX
set_location_assignment PIN_A10 -to UART_CTS
set_location_assignment PIN_A9 -to UART_RTS
set_location_assignment PIN_J8 -to ETH_MDC
set_location_assignment PIN_K8 -to ETH_MDIO
set_location_assignment PIN_N11 -to ETH_MII_COL
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set_location_assignment PIN_L4 -to CODEC_LRCLOCK[1]
set_location_assignment PIN_M4 -to CODEC_DATA_IN[1]
set_location_assignment PIN_L5 -to CODEC_DATA_OUT[1]
set_location_assignment PIN_B4 -to LS_OE
set_location_assignment PIN_H1 -to ADC_IN[0]
set_location_assignment PIN_F1 -to ADC_IN[1]
set_location_assignment PIN_E1 -to ADC_IN[2]
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
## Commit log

2018-12-10 Release v0.2
2018-12-10 Release v0.3.
2018-12-10 Release v0.4.
2018-12-10 Add .png for readme.
2018-12-10 Update README.
2018-12-10 Add schematic pdfs.
2018-12-10 Add board data pdfs.
2018-12-10 Add specifications.
2018-12-10 Add gerfer files for v0.4.
2018-12-10 Add Quartus Prime Project files.
2018-12-13 Add PCB pic.
2018-12-13 Add PCB picture.
2018-12-13 Modify description and specification.
2018-12-13 Add description.
2018-12-13 Add License.
2018-12-20 Release v0.5
    Change C26 from 47uF to 22uF x3.
    Change C1 from 47uF to 10uF x2.
    Change L1 package size.
    Create GND plane on top layer.
2018-12-28 v0.6 resease.
    Add the power switch MIC2005A to reset the ADAU1772.
2018-12-28 Release v0.6
    Add the power switch MIC2005A to reset the ADAU1772.
2019-01-11 Renew the board pictures.
2019-01-11 Resize.
2019-01-11 Add the latest pcb pictures.
2019-01-16 Add connection diagram.
2019-01-16 Renew block diagram.
2019-01-16 Add block diagram
2019-01-16 Add .ai file for block diagram.
2019-01-18 Renew board pics.
2019-01-18 Update PCB photo.
2019-01-18 Add .gitignore.
2019-01-18 Auto stash before merge of "master" and "origin/master"
2019-02-09 Add Avalon-MM Slave to Wishbone Bridge.
2019-02-09 Convert Verilog HDL to VHDL.
2019-02-09 Add OpenCores I2C Core.
2019-02-09 Update SigmaDSP files.
2019-02-09 Renew BSP files.
2019-02-09 Ignore obj directory's file.
2019-02-09 Add header file for OpenCores I2C.
2019-02-09 Modify I2C function for OpenCores I2C Core.
2019-02-09 Update SigmaDSP file.
2019-02-09 Update .qsys_edit directory's files.
2019-02-09 Update Platform Designer files.
2019-02-09 Update .metadata directory's files.
2019-02-09 Update output_files.
2019-02-09 Update software directory.
2019-02-09 Update Quartus Prime files.
2019-02-09 Implemented SigmaDSP communication routine.
2019-02-09 Update .gitignore.
2019-02-09 Add .qws.
2019-02-09 Add .gitattributes.
2019-02-17 Implemented I2S communication(ADAU1761 Master, MAX10 Slave).
2019-02-17 ADAU1761(addr:0x70) is set I2S Master.
    gain set -10dB.
2019-02-17 Updated.
2019-02-18 Supported two ADAU1761(addr:0x70, addr:0x72).
2019-02-18 Set the I2S master to 0x70 and the I2S slave to 0x72
2019-02-18 Set the I2S master to 0x70 and set the I2S slave to 0x72.
2019-02-18 Update.
2019-02-18 Add download function for slave ADAU1761(0x72).
2019-07-23 Add the TSE MAC, mSGDMA(rx & tx) and On-chip RAM(descriptor memory).
2019-07-23 Regenerated.
2019-07-23 Add the readdatavalid and waitreuest.
2019-07-23 Renew
2019-07-23 Recompile
2019-07-23 Swap data_1_mst and data_1_slv.
2019-07-24 Ignore fpga/software/.metadata directory.
2019-07-24 Add bsp files.
2019-07-24 Add FreeRTOS codes.
2019-07-24 Renew.
2019-07-24 Regenerate BSP.
2019-07-24 Refactoring.
2019-07-24 Support FreeRTOS and ETH_OCM(test).
2019-07-24 Add project files.
2019-07-24 Delete.
2019-07-24 Add alt_error_handler.
2019-07-24 Add Open Sound Control(UDP) test code.
2019-07-24 Add elf.
2019-07-24 Add some codes generated by SigmaDSP.
2019-07-24 Add defines header file generated by SigmaDSP.
2019-07-24 add a header file for OpenCores I2C
2019-07-24 Change SSSLED to SigmaDSP.
2019-07-24 Update from v0.4 to v0.6.
2019-07-24 Add some directories and .dat file to ignores.
2019-07-25 Change avalon-mm address width from 28 to 8.
2019-07-25 Reassign Qsys base address and regenerate BSP.
2019-07-26 Stop tracking of fpga/software/.metadata.
2019-07-26 Stop tracking fpga/output_files.
2019-07-26 Add fpga/output_files folder.
2019-07-26 Add Avalon-mm Pipeline Bridge and Clock Bridge.
2019-07-26 Regenerate HDL from Platform Designer.
2019-07-26 Update
    Add avalon-mm pipeline bridge and clock bridge to qsys.
    Connect between i2s_codec.vhd and qsys.
2019-08-01 Wholly modify the I2S process.
    Implement volume control from adc.
2019-08-01 Implement the following functions.
    1. phono equalizer
    2. line/phono switch
    3. channel input gain(-15dB ~ +15dB)
    4. channel 3-band EQ(high:6500hz, mid:1200hz, low:200hz)
    5. master gain(-120dB ~ +10dB)
    6. monitor gain(-120dB ~ +10dB)
2019-08-01 Modify the adc address and interval time.
2019-08-01 Add the osc message "/candy/adc".

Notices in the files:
fpga/CANDY_AVB.qsf:
Copyright (C) 2018  Intel Corporation. All rights reserved.
parts and their libraries:
SparkFun: Licensing: CC v3.0 Share-Alike You are welcome to use this library for commercial purposes.
SparkFun-Connectors: Licensing: Creative Commons ShareAlike 4.0 International - https://creativecommons.org/licenses/by-sa/4.0
